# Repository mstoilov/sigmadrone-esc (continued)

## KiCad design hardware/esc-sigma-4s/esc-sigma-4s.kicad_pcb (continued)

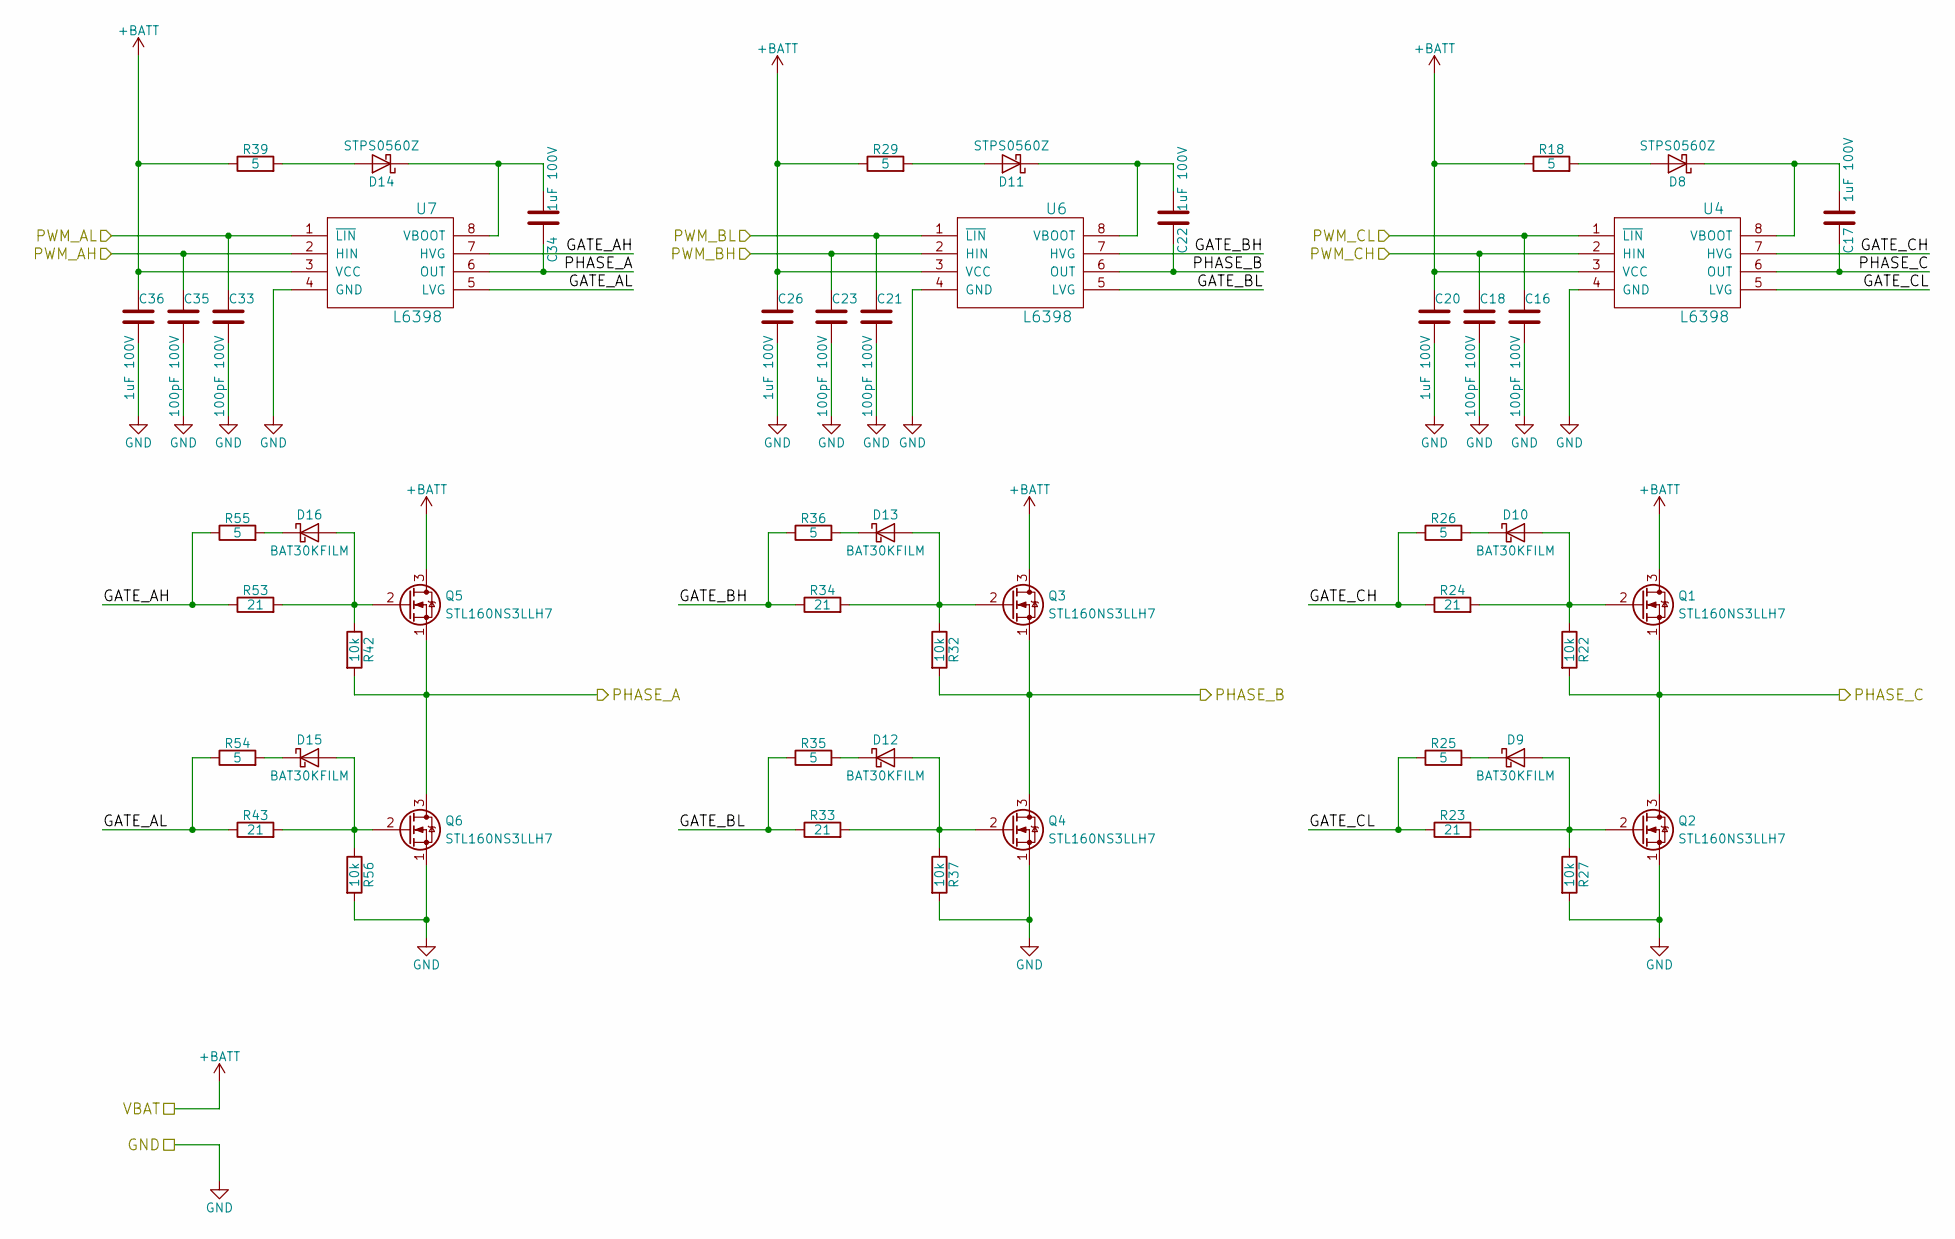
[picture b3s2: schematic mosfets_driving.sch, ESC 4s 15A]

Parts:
C16, C18, C21, C23, C33, C35: 100pF 100V; C_0603; Part 399-7821-2-ND
C17, C20, C22, C26, C34, C36: 1uF 100V; C_0805; Part 445-8887-1-ND
D8, D11, D14: STPS0560Z; D_SOD-123; Part 497-3787-1-ND
D9, D10, D12, D13, D15, D16: BAT30KFILM; D_SOD-523; Part 497-5552-1-ND
Q1, Q2, Q3, Q4, Q5, Q6: STL160NS3LLH7; PQFN_5x6_SGD; Part 497-14988-6-ND
R18, R25, R26, R29, R35, R36, R39, R54, R55: 5; R_0603; Part 311-4.99HRCT-ND
R22, R27, R32, R37, R42, R56: 10k; R_0603; Part 311-10.0KHRCT-ND
R23, R24, R33, R34, R43, R53: 21; R_0603; Part 311-21.0HRCT-ND
U4, U6, U7: L6398; SOIC-8_3.9x4.9mm_Pitch1.27mm; Part 497-16166-5-ND

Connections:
+BATT: C20.2, C26.2, C36.2, Q1.3 (D), Q3.3 (D), Q5.3 (D), R18.1, R29.1, R39.1, U4.3 (VCC), U6.3 (VCC), U7.3 (VCC); also elsewhere on the board
/MCU/PWM_AH: C35.2, U7.2 (HIN); also elsewhere on the board
/MCU/PWM_AL: C33.2, U7.1 (~LIN); also elsewhere on the board
/MCU/PWM_BH: C23.2, U6.2 (HIN); also elsewhere on the board
/MCU/PWM_BL: C21.2, U6.1 (~LIN); also elsewhere on the board
/MCU/PWM_CH: C18.2, U4.2 (HIN); also elsewhere on the board
/MCU/PWM_CL: C16.2, U4.1 (~LIN); also elsewhere on the board
/MOSFETs/GATE_AH: R53.1, R55.1, U7.7 (HVG)
/MOSFETs/GATE_AL: R43.1, R54.1, U7.5 (LVG)
/MOSFETs/GATE_BH: R34.1, R36.1, U6.7 (HVG)
/MOSFETs/GATE_BL: R33.1, R35.1, U6.5 (LVG)
/MOSFETs/GATE_CH: R24.1, R26.1, U4.7 (HVG)
/MOSFETs/GATE_CL: R23.1, R25.1, U4.5 (LVG)
/MOSFETs/PHASE_A: C34.1, Q5.1 (S), Q6.3 (D), R42.2, U7.6 (OUT); also elsewhere on the board
/MOSFETs/PHASE_B: C22.1, Q3.1 (S), Q4.3 (D), R32.2, U6.6 (OUT); also elsewhere on the board
/MOSFETs/PHASE_C: C17.1, Q1.1 (S), Q2.3 (D), R22.2, U4.6 (OUT); also elsewhere on the board
GND: C16.1, C18.1, C20.1, C21.1, C23.1, C26.1, C33.1, C35.1, C36.1, Q2.1 (S), Q4.1 (S), Q6.1 (S), R27.2, R37.2, R56.2, U4.4 (GND), U6.4 (GND), U7.4 (GND); also elsewhere on the board
unnamed: C17.2, D8.1 (K), U4.8 (VBOOT)
unnamed: C22.2, D11.1 (K), U6.8 (VBOOT)
unnamed: C34.2, D14.1 (K), U7.8 (VBOOT)
unnamed: D8.2 (A), R18.2
unnamed: D9.1 (K), R25.2
unnamed: D9.2 (A), Q2.2 (G), R23.2, R27.1
unnamed: D10.1 (K), R26.2
unnamed: D10.2 (A), Q1.2 (G), R22.1, R24.2
unnamed: D11.2 (A), R29.2
unnamed: D12.1 (K), R35.2
unnamed: D12.2 (A), Q4.2 (G), R33.2, R37.1
unnamed: D13.1 (K), R36.2
unnamed: D13.2 (A), Q3.2 (G), R32.1, R34.2
unnamed: D14.2 (A), R39.2
unnamed: D15.1 (K), R54.2
unnamed: D15.2 (A), Q6.2 (G), R43.2, R56.1
unnamed: D16.1 (K), R55.2
unnamed: D16.2 (A), Q5.2 (G), R42.1, R53.2

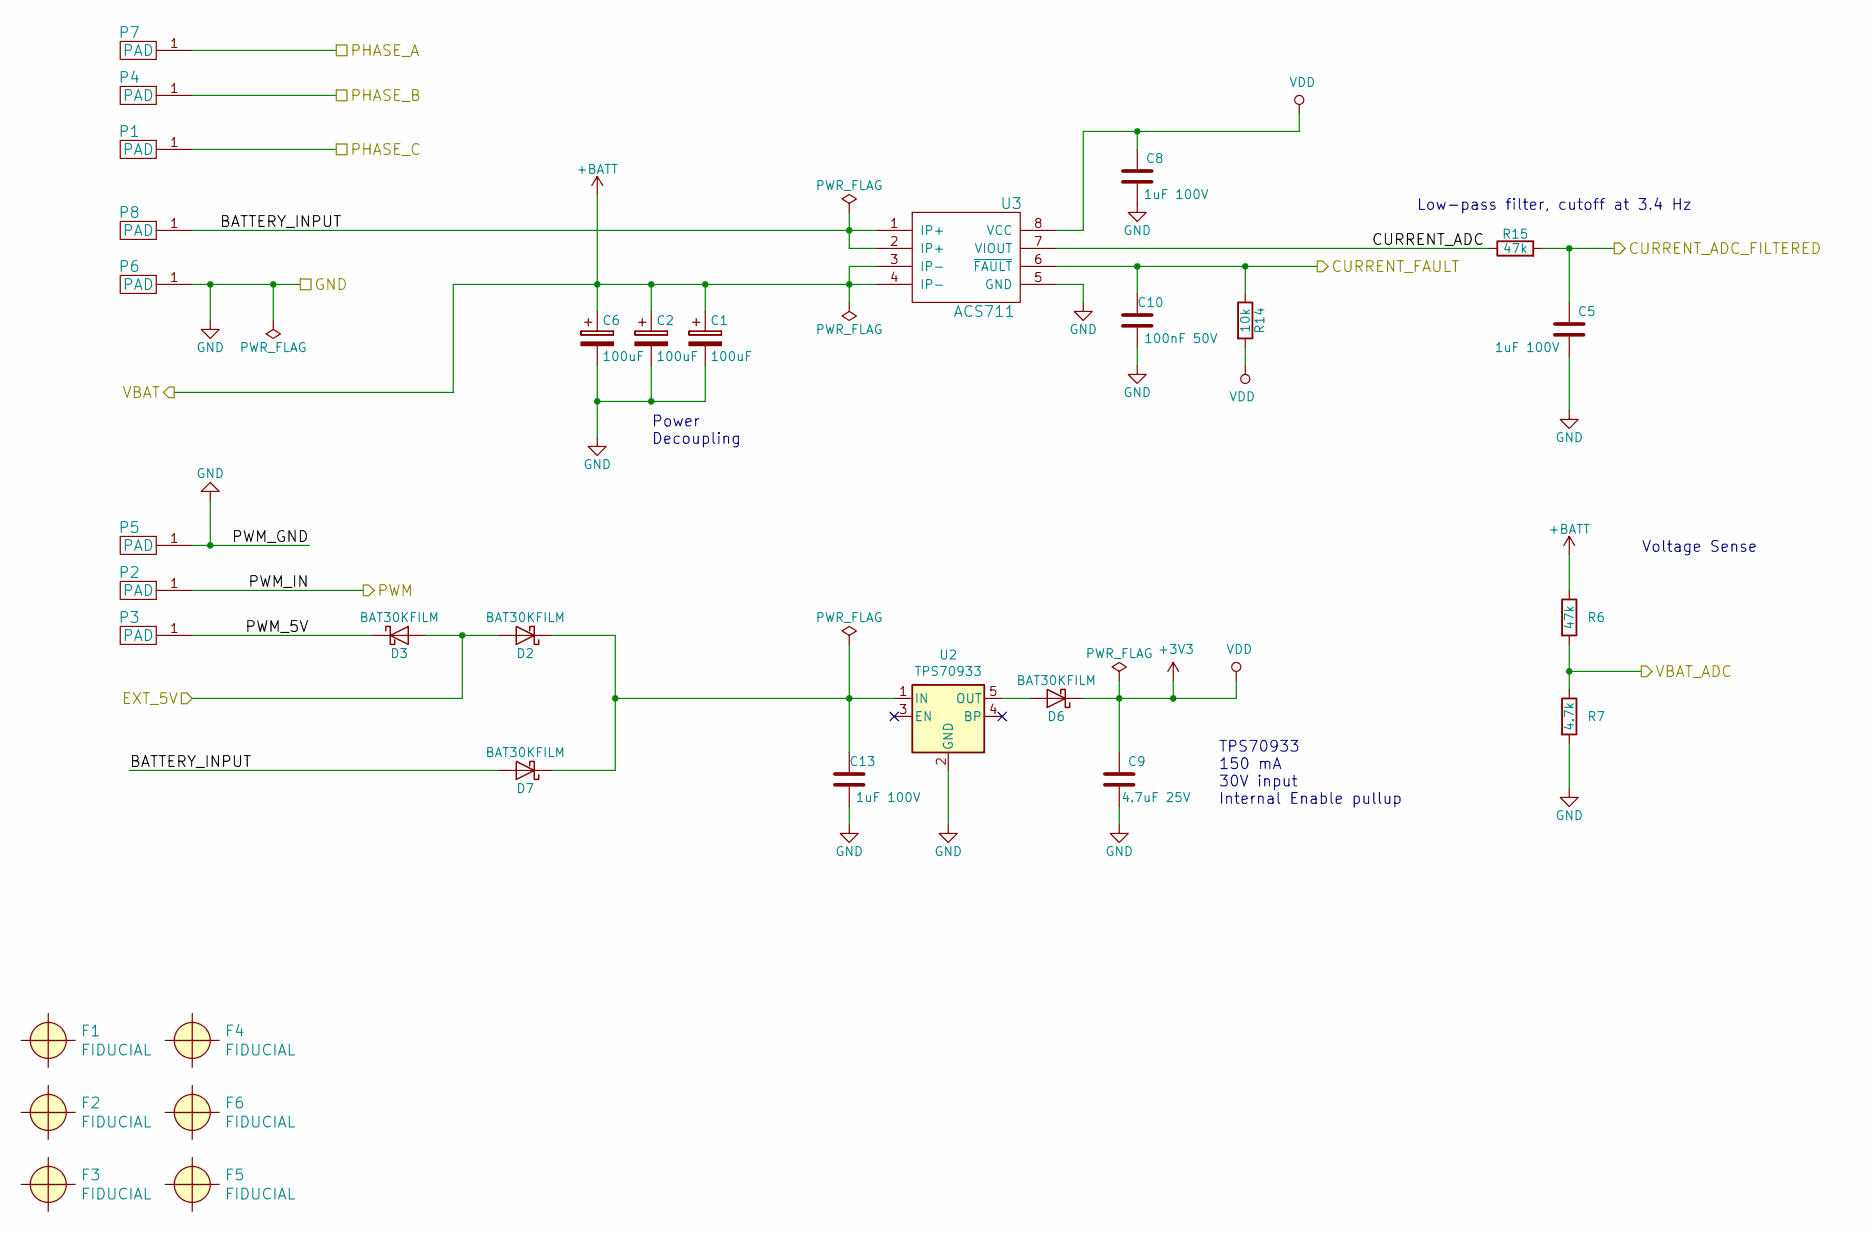
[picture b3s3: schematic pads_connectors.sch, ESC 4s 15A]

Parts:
C1, C2, C6: 100uF; CP_Elec_6.3x7.7; Part 732-8511-1-ND
C5, C8, C13: 1uF 100V; C_0805; Part 445-8887-1-ND
C9: 4.7uF 25V; C_0805; Part 1276-2415-1-ND
C10: 100nF 50V; C_0603; Part 490-4779-2-ND
D2, D3, D6, D7: BAT30KFILM; D_SOD-523; Part 497-5552-1-ND
F1, F2, F3, F4, F5, F6: FIDUCIAL; Fiducial_0.5mm_Dia_1mm_Outer
P1, P4, P6, P7, P8: PAD; SolderWirePad_single_SMD_2x3mm
P2, P3, P5: PAD; SolderWirePad_single_SMD_1.5x2.5mm
R6, R15: 47k; R_0603; Part 311-47KDCT-ND
R7: 4.7k; R_0603; Part 311-2606-2-ND
R14: 10k; R_0603; Part 311-10.0KHRCT-ND
U2: TPS70933; SOT-23-5; Part 296-35483-1-ND
U3: ACS711; SOIC-8_3.9x4.9mm_Pitch1.27mm; Part 620-1373-1-ND

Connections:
+3V3: C8.2, C9.2, D6.1 (K), R14.2, U3.8 (VCC); also elsewhere on the board
+BATT: C1.1, C2.1, C6.1, R6.1, U3.3 (IP-), U3.4 (IP-); also elsewhere on the board
/MCU/CURRENT_ADC: C5.2, R15.2; also elsewhere on the board
/MCU/CURRENT_FAULT: C10.2, R14.1, U3.6 (~FAULT); also elsewhere on the board
/MCU/EXT_5V: D2.2 (A), D3.2 (A); also elsewhere on the board
/MCU/PWM: P2.1; also elsewhere on the board
/MCU/VBAT_ADC: R6.2, R7.1; also elsewhere on the board
/MOSFETs/PHASE_A: P7.1; also elsewhere on the board
/MOSFETs/PHASE_B: P4.1; also elsewhere on the board
/MOSFETs/PHASE_C: P1.1; also elsewhere on the board
/PADS & POWER/BATTERY_INPUT: D7.2 (A), P8.1, U3.1 (IP+), U3.2 (IP+)
/PADS & POWER/CURRENT_ADC: R15.1, U3.7 (VIOUT)
/PADS & POWER/PWM_5V: D3.1 (K), P3.1
GND: C1.2, C2.2, C5.1, C6.2, C8.1, C9.1, C10.1, C13.1, P5.1, P6.1, R7.2, U2.2 (GND), U3.5 (GND); also elsewhere on the board
unnamed: C13.2, D2.1 (K), D7.1 (K), U2.1 (IN)
unnamed: D6.2 (A), U2.5 (OUT)

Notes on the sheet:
Low-pass filter, cutoff at 3.4 Hz
Power Decoupling
Voltage Sense
TPS70933 150 mA 30V input Internal Enable pullup

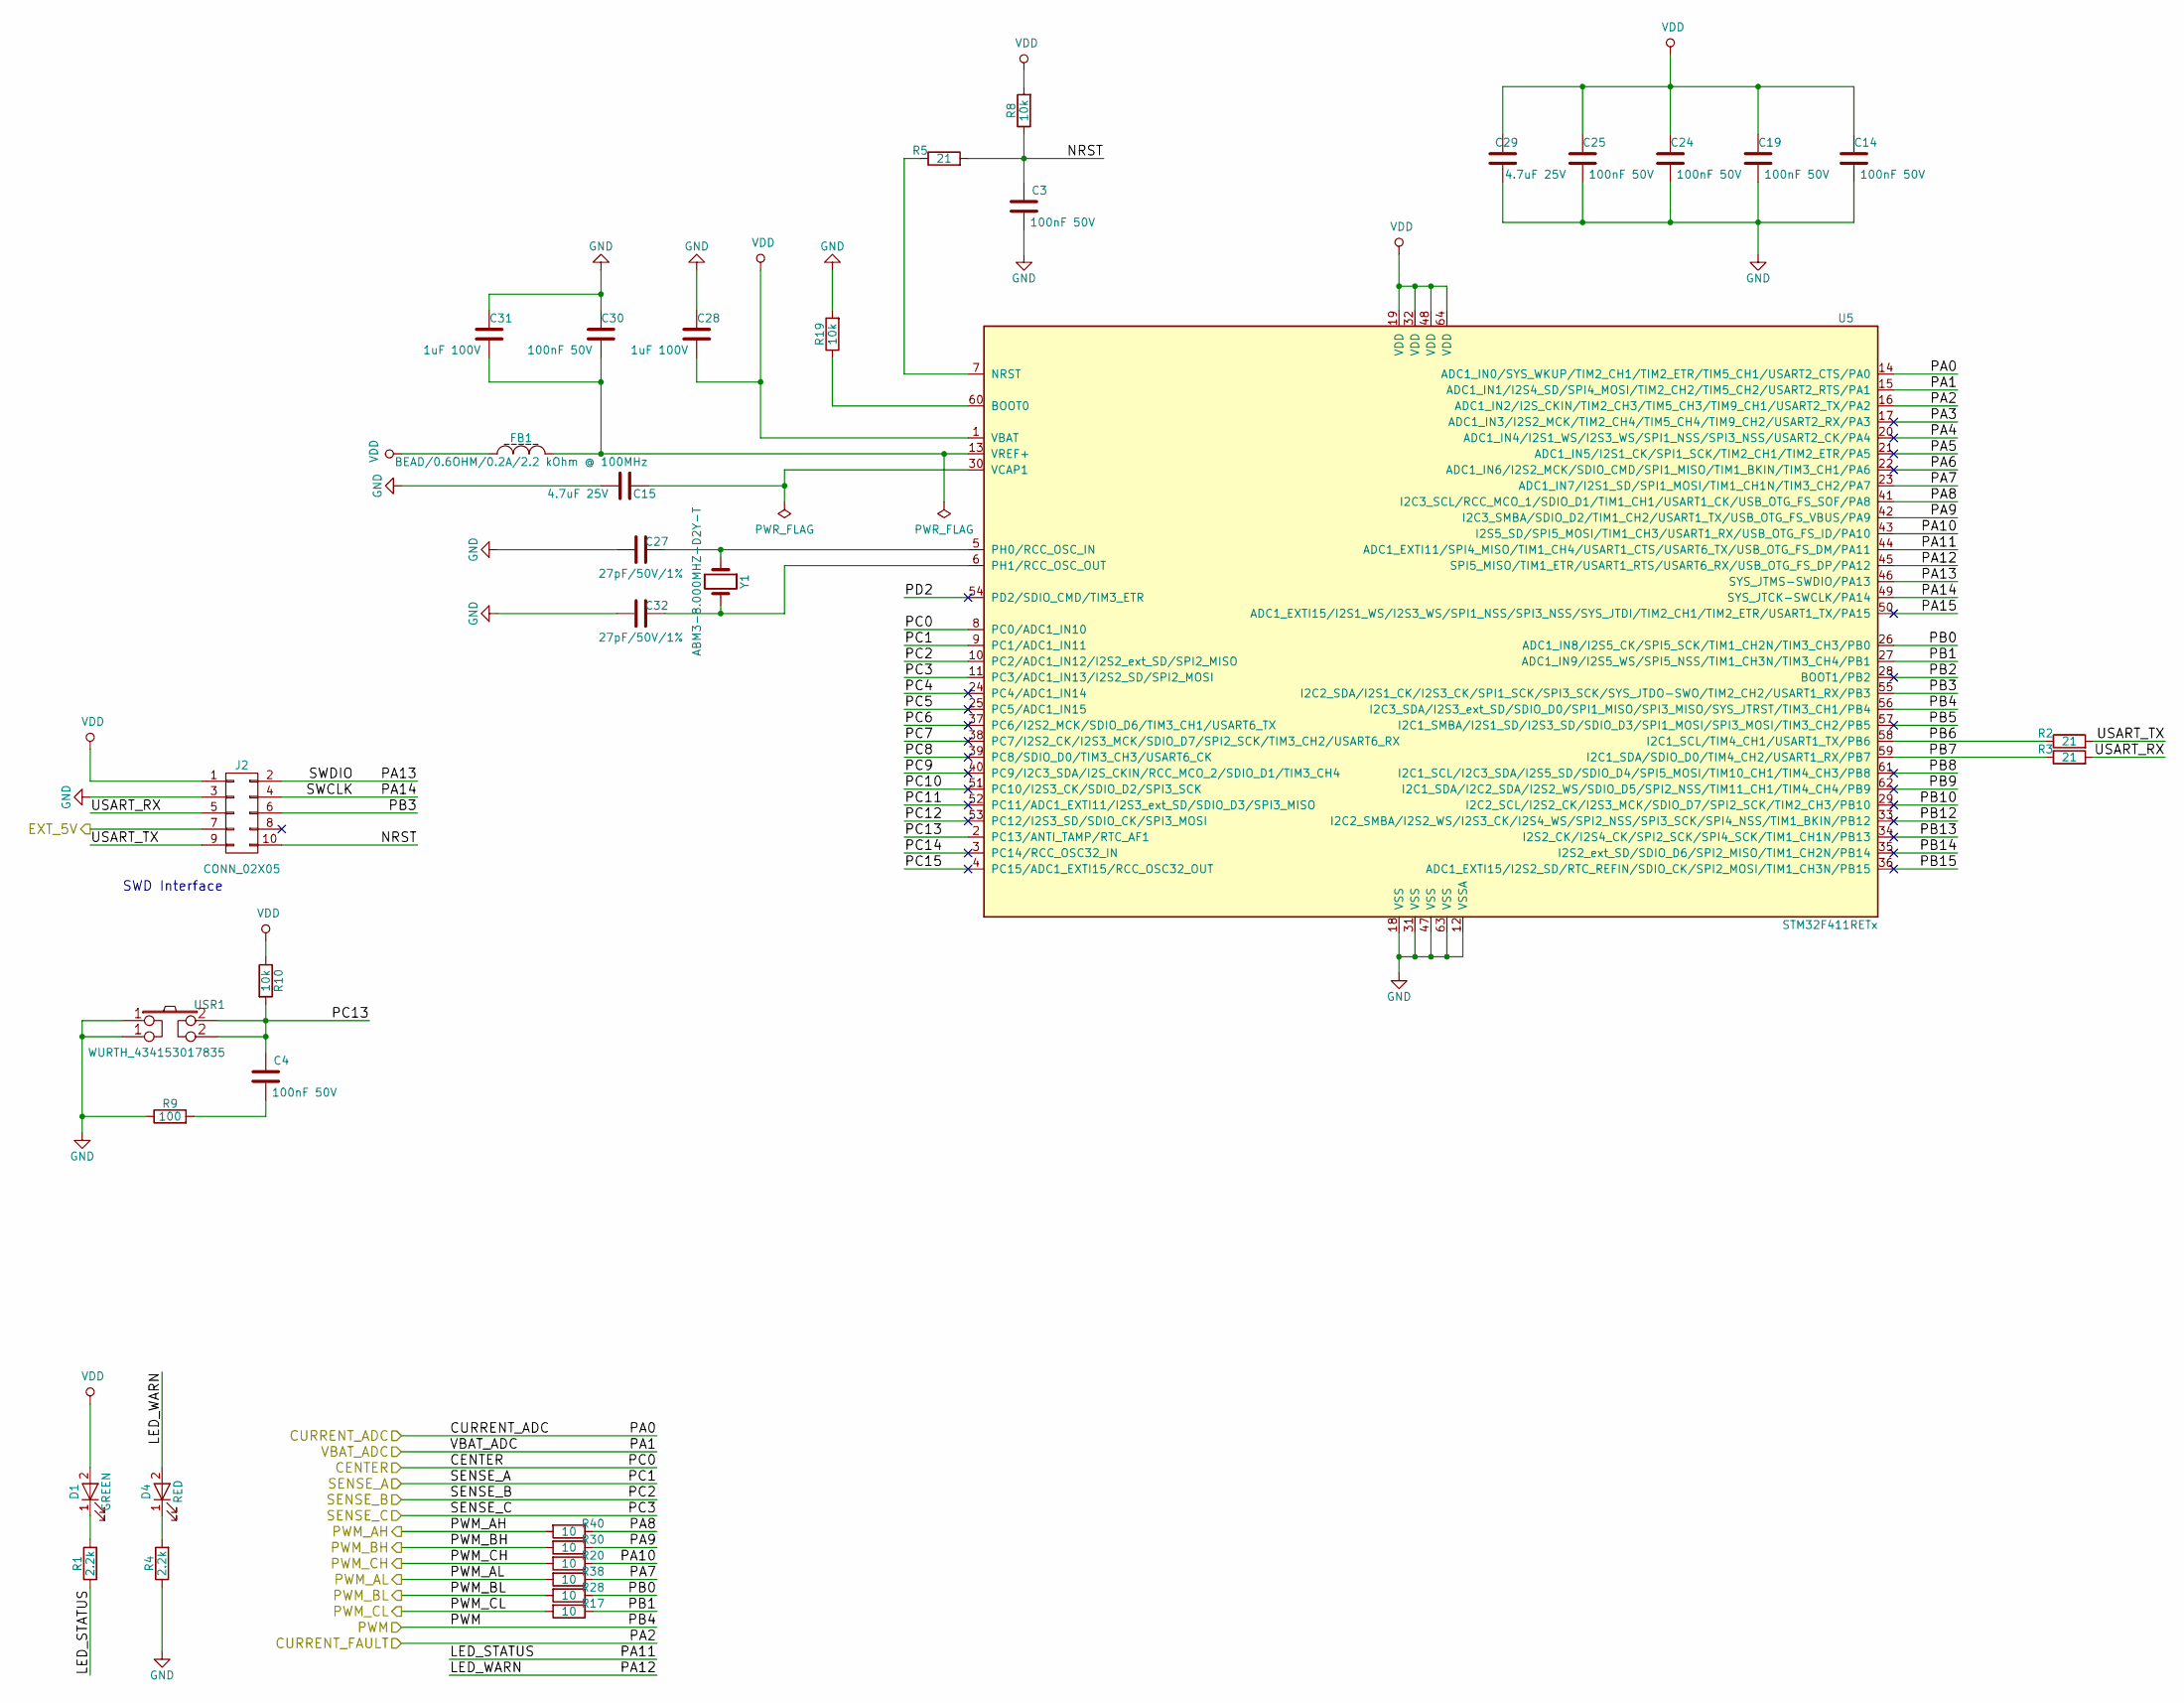
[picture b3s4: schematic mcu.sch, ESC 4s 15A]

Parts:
C3, C4, C14, C19, C24, C25, C30: 100nF 50V; C_0603; Part 490-4779-2-ND
C15, C29: 4.7uF 25V; C_0805; Part 1276-2415-1-ND
C27, C32: 27pF/50V/1%; C_0603; Part 490-9719-1-ND
C28, C31: 1uF 100V; C_0805; Part 445-8887-1-ND
D1: GREEN; LED_0603; Part 732-4971-1-ND
D4: RED; LED_0603; Part 732-4978-1-ND
FB1: BEAD/0.6OHM/0.2A/2.2 kOhm @ 100MHz; R_0805; Part 732-1609-1-ND
J2: CONN_02X05; Pin_Header_Straight_2x05_Pitch1.27mm; Part 732-5374-ND
R1, R4: 2.2k; R_0603; Part RMCF0603JT2K20CT-ND
R2, R3, R5: 21; R_0603; Part 311-21.0HRCT-ND
R8, R10, R19: 10k; R_0603; Part 311-10.0KHRCT-ND
R9: 100; R_0603; Part 311-100HRCT-ND
R17, R20, R28, R30, R38, R40: 10; R_0603; Part 311-10.0HRCT-ND
U5: STM32F411RETx; LQFP-64_10x10mm_Pitch0.5mm; Part 497-14909-ND
USR1: WURTH_434153017835; SW_SPST_WURTH_434153017835; Part 732-10143-1-ND
Y1: ABM3-8.000MHZ-D2Y-T; Crystal_SMD_Abracon_ABM3-2pin_5.0x3.2mm; Part 535-10630-1-ND

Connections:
+3V3: C14.2, C19.2, C24.2, C25.2, C28.1, C29.2, D1.2 (A), FB1.1, J2.1, R8.2, R10.1, U5.1 (VBAT), U5.19 (VDD), U5.32 (VDD), U5.48 (VDD), U5.64 (VDD); also elsewhere on the board
/MCU/CENTER: U5.8 (PC0/ADC1_IN10); also elsewhere on the board
/MCU/CURRENT_ADC: U5.14 (ADC1_IN0/SYS_WKUP/TIM2_CH1/TIM2_ETR/TIM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); also elsewhere on the board
/MCU/CURRENT_FAULT: U5.16 (ADC1_IN2/I2S_CKIN/TIM2_CH3/TIM5_CH3/TIM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); also elsewhere on the board
/MCU/EXT_5V: J2.7; also elsewhere on the board
/MCU/LED_STATUS: R1.1, U5.44 (ADC1_EXTI11/SPI4_MISO/TIM1_CH4/USART1_C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)
/MCU/LED_WARN: D4.2 (A), U5.45 (SPI5_MISO/TIM1_ETR/USART1_RTS/USART6_RX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)
/MCU/NRST: C3.2, J2.10, R5.2, R8.1
/MCU/PA3: U5.17 (ADC1_IN3/I2S2_MCK/TIM2_CH4/TIM5_CH4/TIM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)
/MCU/PA4: U5.20 (ADC1_IN4/I2S1_WS/I2S3_WS/SPI1_NSS/SPI3_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)
/MCU/PA5: U5.21 (ADC1_IN5/I2S1_CK/SPI1_SCK/TIM2_CH1/TIM2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)
/MCU/PA6: U5.22 (ADC1_IN6/I2S2_MCK/SDIO_CMD/SPI1_MISO/TI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)
/MCU/PA7: R38.1, U5.23 (ADC1_IN7/I2S1_SD/SPI1_MOSI/TIM1_CH1N/TI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)
/MCU/PA8: R40.1, U5.41 (I2C3_SCL/RCC_MCO_1/SDIO_D1/TIM1_CH1/USA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)
/MCU/PA9: R30.1, U5.42 (I2C3_SMBA/SDIO_D2/TIM1_CH2/USART1_TX/US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)
/MCU/PA10: R20.1, U5.43 (I2S5_SD/SPI5_MOSI/TIM1_CH3/USART1_RX/US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)
/MCU/PA13: J2.2, U5.46 (SYS_JTMS-SWDIO/PA13)
/MCU/PA14: J2.4, U5.49 (SYS_JTCK-SWCLK/PA14)
/MCU/PA15: U5.50 (ADC1_EXTI15/I2S1_WS/I2S3_WS/SPI1_NSS/SP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)
/MCU/PB0: R28.1, U5.26 (ADC1_IN8/I2S5_CK/SPI5_SCK/TIM1_CH2N/TIM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)
/MCU/PB1: R17.1, U5.27 (ADC1_IN9/I2S5_WS/SPI5_NSS/TIM1_CH3N/TIM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)
/MCU/PB2: U5.28 (BOOT1/PB2)
/MCU/PB3: J2.6, U5.55 (I2C2_SDA/I2S1_CK/I2S3_CK/SPI1_SCK/SPI3_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)
/MCU/PB5: U5.57 (I2C1_SMBA/I2S1_SD/I2S3_SD/SDIO_D3/SPI1_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)
/MCU/PB6: R2.1, U5.58 (I2C1_SCL/TIM4_CH1/USART1_TX/PB6)
/MCU/PB7: R3.1, U5.59 (I2C1_SDA/SDIO_D0/TIM4_CH2/USART1_RX/PB7)
/MCU/PB8: U5.61 (I2C1_SCL/I2C3_SDA/I2S5_SD/SDIO_D4/SPI5_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)
/MCU/PB9: U5.62 (I2C1_SDA/I2C2_SDA/I2S2_WS/SDIO_D5/SPI2_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)
/MCU/PB10: U5.29 (I2C2_SCL/I2S2_CK/I2S3_MCK/SDIO_D7/SPI2_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)
/MCU/PB12: U5.33 (I2C2_SMBA/I2S2_WS/I2S3_CK/I2S4_WS/SPI2_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)
/MCU/PB13: U5.34 (I2S2_CK/I2S4_CK/SPI2_SCK/SPI4_SCK/TIM1_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)
/MCU/PB14: U5.35 (I2S2_ext_SD/SDIO_D6/SPI2_MISO/TIM1_CH2N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)
/MCU/PB15: U5.36 (ADC1_EXTI15/I2S2_SD/RTC_REFIN/SDIO_CK/S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)
/MCU/PC4: U5.24 (PC4/ADC1_IN14)
/MCU/PC5: U5.25 (PC5/ADC1_IN15)
/MCU/PC6: U5.37 (PC6/I2S2_MCK/SDIO_D6/TIM3_CH1/USART6_TX)
/MCU/PC7: U5.38 (PC7/I2S2_CK/I2S3_MCK/SDIO_D7/SPI2_SCK/T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)
/MCU/PC8: U5.39 (PC8/SDIO_D0/TIM3_CH3/USART6_CK)
/MCU/PC9: U5.40 (PC9/I2C3_SDA/I2S_CKIN/RCC_MCO_2/SDIO_D1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)
/MCU/PC10: U5.51 (PC10/I2S3_CK/SDIO_D2/SPI3_SCK)
/MCU/PC11: U5.52 (PC11/ADC1_EXTI11/I2S3_ext_SD/SDIO_D3/SP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)
/MCU/PC12: U5.53 (PC12/I2S3_SD/SDIO_CK/SPI3_MOSI)
/MCU/PC13: C4.2, R10.2, U5.2 (PC13/ANTI_TAMP/RTC_AF1), USR1.2
/MCU/PC14: U5.3 (PC14/RCC_OSC32_IN)
/MCU/PC15: U5.4 (PC15/ADC1_EXTI15/RCC_OSC32_OUT)
/MCU/PD2: U5.54 (PD2/SDIO_CMD/TIM3_ETR)
/MCU/PWM: U5.56 (I2C3_SDA/I2S3_ext_SD/SDIO_D0/SPI1_MISO/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); also elsewhere on the board
/MCU/PWM_AH: R40.2; also elsewhere on the board
/MCU/PWM_AL: R38.2; also elsewhere on the board
/MCU/PWM_BH: R30.2; also elsewhere on the board
/MCU/PWM_BL: R28.2; also elsewhere on the board
/MCU/PWM_CH: R20.2; also elsewhere on the board
/MCU/PWM_CL: R17.2; also elsewhere on the board
/MCU/SENSE_A: U5.9 (PC1/ADC1_IN11); also elsewhere on the board
/MCU/SENSE_B: U5.10 (PC2/ADC1_IN12/I2S2_ext_SD/SPI2_MISO); also elsewhere on the board
/MCU/SENSE_C: U5.11 (PC3/ADC1_IN13/I2S2_SD/SPI2_MOSI); also elsewhere on the board
/MCU/USART_RX: J2.5, R3.2
/MCU/USART_TX: J2.9, R2.2
/MCU/VBAT_ADC: U5.15 (ADC1_IN1/I2S4_SD/SPI4_MOSI/TIM2_CH2/TIM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); also elsewhere on the board
GND: C3.1, C14.1, C15.1, C19.1, C24.1, C25.1, C27.2, C28.2, C29.1, C30.2, C31.2, C32.2, J2.3, R4.1, R9.1, R19.2, U5.12 (VSSA), U5.18 (VSS), U5.31 (VSS), U5.47 (VSS), U5.63 (VSS), USR1.1; also elsewhere on the board
unnamed: C4.1, R9.2
unnamed: C15.2, U5.30 (VCAP1)
unnamed: C27.1, U5.5 (PH0/RCC_OSC_IN), Y1.1
unnamed: C30.1, C31.1, FB1.2, U5.13 (VREF+)
unnamed: C32.1, U5.6 (PH1/RCC_OSC_OUT), Y1.2
unnamed: D1.1 (K), R1.2
unnamed: D4.1 (K), R4.2
unnamed: R5.1, U5.7 (NRST)
unnamed: R19.1, U5.60 (BOOT0)

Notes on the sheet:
SWD Interface

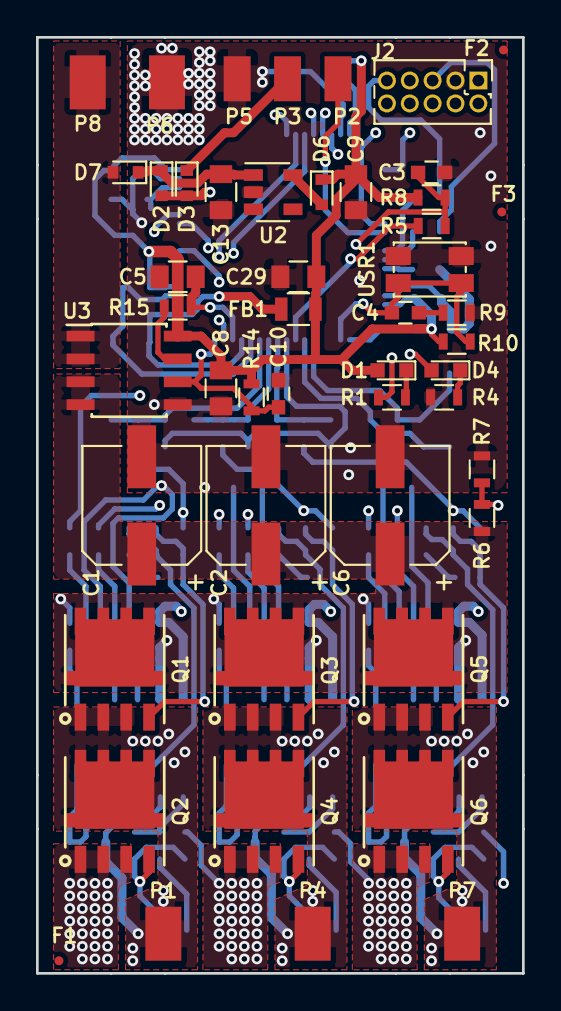
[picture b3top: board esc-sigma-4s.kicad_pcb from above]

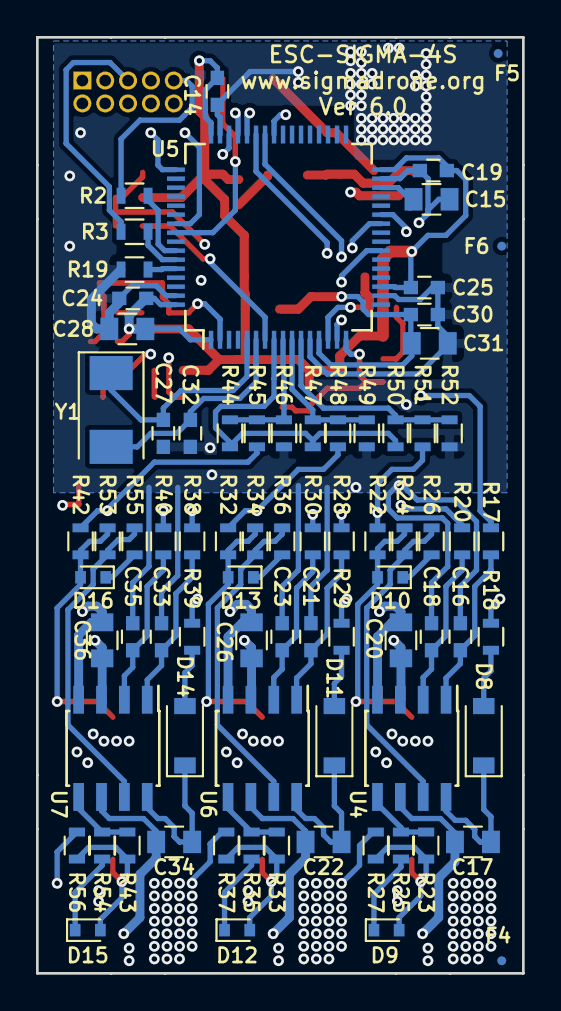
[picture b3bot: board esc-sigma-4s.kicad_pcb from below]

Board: 4 copper layers, 27.0 x 52.0 mm, 127 parts (78 on the bottom side), 76 nets.

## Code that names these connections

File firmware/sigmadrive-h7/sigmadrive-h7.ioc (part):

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Mcu.Name=STM32H743VGTx
Mcu.Package=LQFP100
Mcu.UserName=STM32H743VGTx
PA0.GPIOParameters=GPIO_Label
PA0.GPIO_Label=PULSE_M2/TIM5_CH1
PA0.Signal=S_TIM5_CH1
PA1.GPIOParameters=GPIO_PuPd,GPIO_Label,GPIO_Mode
PA1.GPIO_Label=M1_SOA/M1_IA_FB
PA1.GPIO_Mode=GPIO_MODE_ANALOG
PA1.GPIO_PuPd=GPIO_NOPULL
PA1.Mode=IN17-Single-Ended
PA1.Signal=ADC1_INP17
PA10.GPIOParameters=GPIO_Speed,GPIO_Label
PA10.GPIO_Label=DBG_USART1_TX
PA10.GPIO_Speed=GPIO_SPEED_FREQ_VERY_HIGH
PA10.Mode=Asynchronous
PA10.Signal=USART1_RX
PA11.GPIOParameters=GPIO_Label
PA11.GPIO_Label=USB_DM
PA11.Mode=Device_Only
PA11.Signal=USB_OTG_FS_DM
PA12.GPIOParameters=GPIO_Label
PA12.GPIO_Label=USB_DP
PA12.Mode=Device_Only
PA12.Signal=USB_OTG_FS_DP
PA13\ (JTMS/SWDIO).Signal=DEBUG_JTMS-SWDIO
PA14\ (JTCK/SWCLK).Signal=DEBUG_JTCK-SWCLK
PA2.GPIOParameters=GPIO_PuPd,GPIO_Label,GPIO_Mode
PA2.GPIO_Label=M1_SOB/M1_IB_FB
PA2.GPIO_Mode=GPIO_MODE_ANALOG
PA2.GPIO_PuPd=GPIO_NOPULL
PA2.Signal=ADCx_INP14
PA3.GPIOParameters=GPIO_PuPd,GPIO_Label,GPIO_Mode
PA3.GPIO_Label=ANALOG_SPEED_CTRL
PA3.GPIO_Mode=GPIO_MODE_ANALOG
PA3.GPIO_PuPd=GPIO_NOPULL
PA3.Signal=ADCx_INP15
PA4.GPIOParameters=GPIO_PuPd,GPIO_Label,GPIO_Mode
PA4.GPIO_Label=M1_SOC/M1_IC_FB
PA4.GPIO_Mode=GPIO_MODE_ANALOG
PA4.GPIO_PuPd=GPIO_NOPULL
PA4.Signal=ADCx_INP18
PA5.GPIOParameters=GPIO_Label
PA5.GPIO_Label=PULSE_M1/TIM2_CH1
PA5.Signal=S_TIM2_CH1_ETR
PA6.GPIOParameters=GPIO_PuPd,GPIO_Label,GPIO_Mode
PA6.GPIO_Label=VBAT_ADC
PA6.GPIO_Mode=GPIO_MODE_ANALOG
PA6.GPIO_PuPd=GPIO_NOPULL
PA6.Signal=ADCx_INP3
PA7.GPIOParameters=GPIO_Label
PA7.GPIO_Label=M2_AL
PA7.Mode=PWM Generation1 CH1 CH1N
PA7.Signal=TIM8_CH1N
PA9.GPIOParameters=GPIO_Speed,GPIO_Label
PA9.GPIO_Label=DBG_USART1_RX
PA9.GPIO_Speed=GPIO_SPEED_FREQ_VERY_HIGH
PA9.Mode=Asynchronous
PA9.Signal=USART1_TX
PB0.Signal=S_TIM3_CH3
PB1.GPIOParameters=GPIO_Label
PB1.GPIO_Label=M2_CL
PB1.Mode=PWM Generation3 CH3 CH3N
PB1.Signal=TIM8_CH3N
PB10.Mode=Full_Duplex_Master
PB10.Signal=SPI2_SCK
PB11.GPIOParameters=GPIO_Label
PB11.GPIO_Label=QUAD_Z_M1
PB11.Signal=GPXTI11
PB12.GPIOParameters=GPIO_Label
PB12.GPIO_Label=OUTPUT_1
PB12.Signal=GPIO_Output
PB13.GPIOParameters=GPIO_Label
PB13.GPIO_Label=OUTPUT_2
PB13.Signal=GPIO_Output
PB14.GPIOParameters=GPIO_Label
PB14.GPIO_Label=M2_BL
PB14.Mode=PWM Generation2 CH2 CH2N
PB14.Signal=TIM8_CH2N
PB15.GPIOParameters=GPIO_Label
PB15.GPIO_Label=DRV_SDI
PB15.Mode=Full_Duplex_Master
PB15.Signal=SPI2_MOSI
PB2.GPIOParameters=GPIO_Label
PB2.GPIO_Label=GATE_M2_ENABLE
PB2.Signal=GPIO_Output
PB3\ (JTDO/TRACESWO).Signal=DEBUG_JTDO-SWO
PB4\ (NJTRST).GPIOParameters=GPIO_Label
PB4\ (NJTRST).GPIO_Label=QUAD_A_M1
PB4\ (NJTRST).Signal=S_TIM3_CH1
PB5.GPIOParameters=GPIO_Label
PB5.GPIO_Label=QUAD_B_M1
PB5.Signal=S_TIM3_CH2
PB6.GPIOParameters=GPIO_Label
PB6.GPIO_Label=QUAD_A_M2
PB6.Signal=S_TIM4_CH1
PB7.GPIOParameters=GPIO_Label
PB7.GPIO_Label=QUAD_B_M2
PB7.Signal=S_TIM4_CH2
PB8.Signal=S_TIM4_CH3
PC0.GPIOParameters=GPIO_Label
PC0.GPIO_Label=M2_SOA/M2_IA_FB
PC0.Signal=ADCx_INP10
PC1.GPIOParameters=GPIO_Label
PC1.GPIO_Label=M2_SOB/M2_IB_FB
PC1.Signal=ADCx_INP11
PC10.GPIOParameters=GPIO_Label
PC10.GPIO_Label=TD_422/UART4
PC10.Mode=Asynchronous
PC10.Signal=UART4_TX
PC11.GPIOParameters=GPIO_Label
PC11.GPIO_Label=RD_422/UART4
PC11.Mode=Asynchronous
PC11.Signal=UART4_RX
PC12.GPIOParameters=GPIO_Label
PC12.GPIO_Label=BRAKE_B_RELEASE
PC12.Signal=GPIO_Output
PC13.GPIOParameters=GPIO_Label
PC13.GPIO_Label=DRV1_CS
PC13.Signal=GPIO_Output
PC14-OSC32_IN\ (OSC32_IN).GPIOParameters=GPIO_Label
PC14-OSC32_IN\ (OSC32_IN).GPIO_Label=DRV2_CS
PC14-OSC32_IN\ (OSC32_IN).Signal=GPIO_Output
PC15-OSC32_OUT\ (OSC32_OUT).GPIOParameters=GPIO_Label
PC15-OSC32_OUT\ (OSC32_OUT).GPIO_Label=DRV_FAULT\#
PC15-OSC32_OUT\ (OSC32_OUT).Signal=GPIO_Input
PC2_C.GPIOParameters=GPIO_Label
PC2_C.GPIO_Label=DRV_SDO
PC2_C.Mode=Full_Duplex_Master
PC2_C.Signal=SPI2_MISO
PC3_C.GPIOParameters=GPIO_Label
PC3_C.GPIO_Label=M2_SOC/M2_IC_FB
PC3_C.Mode=IN1-Single-Ended
PC3_C.Signal=ADC3_INP1
PC4.GPIOParameters=GPIO_PuPd,GPIO_Label,GPIO_Mode
PC4.GPIO_Label=TEMP2
PC4.GPIO_Mode=GPIO_MODE_ANALOG
PC4.GPIO_PuPd=GPIO_NOPULL
PC4.Signal=ADCx_INP4
PC5.GPIOParameters=GPIO_PuPd,GPIO_Label,GPIO_Mode
PC5.GPIO_Label=TEMP1
PC5.GPIO_Mode=GPIO_MODE_ANALOG
PC5.GPIO_PuPd=GPIO_NOPULL
PC5.Signal=ADCx_INP8
PC6.GPIOParameters=GPIO_Label
PC6.GPIO_Label=M2_AH
PC6.Signal=S_TIM8_CH1
PC7.GPIOParameters=GPIO_Label
PC7.GPIO_Label=M2_BH
PC7.Signal=S_TIM8_CH2
PC8.GPIOParameters=GPIO_Label
PC8.GPIO_Label=M2_CH
PC8.Signal=S_TIM8_CH3
PC9.GPIOParameters=GPIO_Label
PC9.GPIO_Label=LED_STATUS
PC9.Signal=GPIO_Output
PD0.GPIOParameters=GPIO_Label
PD0.GPIO_Label=CAR_RX
PD0.Mode=FDCAN_Activate
PD0.Signal=FDCAN1_RX
PD1.GPIOParameters=GPIO_Label
PD1.GPIO_Label=CAN_TX
PD1.Mode=FDCAN_Activate
PD1.Signal=FDCAN1_TX
PD10.GPIOParameters=GPIO_Label
PD10.GPIO_Label=M1_SW1
PD10.Signal=GPIO_Input
PD11.GPIOParameters=GPIO_Label
PD11.GPIO_Label=M1_SW2
PD11.Signal=GPIO_Input
PD12.GPIOParameters=GPIO_Label
PD12.GPIO_Label=ENCODER_DE_M1
PD12.Mode=Hardware Flow Control (RS485)
PD12.Signal=USART3_DE
PD13.GPIOParameters=GPIO_Label
PD13.GPIO_Label=DIRECTION_A
PD13.Signal=GPIO_Input
PD14.GPIOParameters=GPIO_Label
PD14.GPIO_Label=LED_WARN
PD14.Signal=GPIO_Output
PD15.GPIOParameters=GPIO_Label
PD15.GPIO_Label=DIRECTION_B
PD15.Signal=GPIO_Input
PD2.GPIOParameters=GPIO_Label
PD2.GPIO_Label=M2_SW1
PD2.Signal=GPIO_Input
PD3.GPIOParameters=GPIO_Label
PD3.GPIO_Label=M2_SW2
PD3.Signal=GPIO_Input
PD4.GPIOParameters=GPIO_Label
PD4.GPIO_Label=ENCODER_DE_M2
PD4.Mode=Hardware Flow Control (RS485)
PD4.Signal=USART2_DE
PD5.GPIOParameters=GPIO_Label
PD5.GPIO_Label=ENCODER_DI_M2
PD5.Mode=Asynchronous
PD5.Signal=USART2_TX
PD6.GPIOParameters=GPIO_Label
PD6.GPIO_Label=ENCODER_RO_M2
PD6.Mode=Asynchronous
PD6.Signal=USART2_RX
PD7.GPIOParameters=GPIO_Label
PD7.GPIO_Label=QUAD_Z_M2
PD7.Signal=GPXTI7
PD8.GPIOParameters=GPIO_Label
PD8.GPIO_Label=ENCODER_DI_M1
PD8.Mode=Asynchronous
PD8.Signal=USART3_TX
PD9.GPIOParameters=GPIO_Label
PD9.GPIO_Label=ENCODER_RO_M1
PD9.Mode=Asynchronous
PD9.Signal=USART3_RX
PE0.GPIOParameters=GPIO_Speed
PE0.GPIO_Speed=GPIO_SPEED_FREQ_VERY_HIGH
PE0.Mode=Asynchronous
PE0.Signal=UART8_RX
PE1.GPIOParameters=GPIO_Speed
PE1.GPIO_Speed=GPIO_SPEED_FREQ_VERY_HIGH
PE1.Mode=Asynchronous
PE1.Signal=UART8_TX
PE10.GPIOParameters=GPIO_Label
PE10.GPIO_Label=M1_BL
PE10.Mode=PWM Generation2 CH2 CH2N
PE10.Signal=TIM1_CH2N
PE11.GPIOParameters=GPIO_Label
PE11.GPIO_Label=M1_BH
PE11.Signal=S_TIM1_CH2
PE12.GPIOParameters=GPIO_Label
PE12.GPIO_Label=M1_CL
PE12.Mode=PWM Generation3 CH3 CH3N
PE12.Signal=TIM1_CH3N
PE13.GPIOParameters=GPIO_Label
PE13.GPIO_Label=M1_CH
PE13.Signal=S_TIM1_CH3
PE14.GPIOParameters=GPIO_Label
PE14.GPIO_Label=DRV_CAL
PE14.Signal=GPIO_Output
PE15.GPIOParameters=GPIO_Label
PE15.GPIO_Label=GATE_M1_ENABLE
PE15.Signal=GPIO_Output
PE2.GPIOParameters=GPIO_Label
PE2.GPIO_Label=INPUT_1\#
PE2.Signal=GPIO_Input
PE4.GPIOParameters=GPIO_Label
PE4.GPIO_Label=INPUT_2\#
PE4.Signal=GPIO_Input
PE5.GPIOParameters=GPIO_Label
PE5.GPIO_Label=BRAKE_A_FB
PE5.Signal=GPIO_Input
PE6.GPIOParameters=GPIO_Label
PE6.GPIO_Label=BRAKE_B_FB
PE6.Signal=GPIO_Input
PE8.GPIOParameters=GPIO_Label
PE8.GPIO_Label=M1_AL
PE8.Mode=PWM Generation1 CH1 CH1N
PE8.Signal=TIM1_CH1N
PE9.GPIOParameters=GPIO_Label
PE9.GPIO_Label=M1_AH
PE9.Signal=S_TIM1_CH1
PH0-OSC_IN\ (PH0).Mode=HSE-External-Oscillator
PH0-OSC_IN\ (PH0).Signal=RCC_OSC_IN
PH1-OSC_OUT\ (PH1).Mode=HSE-External-Oscillator
PH1-OSC_OUT\ (PH1).Signal=RCC_OSC_OUT
RCC.HSE_VALUE=12000000
RCC.SYSCLKFreq_VALUE=480000000
RCC.SYSCLKSource=RCC_SYSCLKSOURCE_PLLCLK
board=custom

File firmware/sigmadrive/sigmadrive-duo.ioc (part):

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Mcu.Name=STM32F745V(E-G)Tx
Mcu.Package=LQFP100
Mcu.UserName=STM32F745VGTx
PA0/WKUP.Signal=S_TIM5_CH1
PA1.GPIOParameters=GPIO_Label
PA1.GPIO_Label=M1_IA_FB
PA1.Signal=ADCx_IN1
PA10.Mode=Asynchronous
PA10.Signal=USART1_RX
PA11.Mode=Device_Only
PA11.Signal=USB_OTG_FS_DM
PA12.Mode=Device_Only
PA12.Signal=USB_OTG_FS_DP
PA15.Mode=Hardware Flow Control (RS485)
PA15.Signal=UART4_DE
PA2.GPIOParameters=GPIO_Label
PA2.GPIO_Label=M1_IB_FB
PA2.Signal=ADCx_IN2
PA3.GPIOParameters=GPIO_Label
PA3.GPIO_Label=ADC3_IN3
PA3.Signal=ADCx_IN3
PA4.GPIOParameters=GPIO_Label
PA4.GPIO_Label=M1_IC_FB
PA4.Signal=ADCx_IN4
PA5.Signal=S_TIM2_CH1_ETR
PA6.Signal=ADCx_IN6
PA7.Mode=PWM Generation1 CH1 CH1N
PA7.Signal=TIM8_CH1N
PA9.Mode=Asynchronous
PA9.Signal=USART1_TX
PB0.Signal=S_TIM3_CH3
PB1.Mode=PWM Generation3 CH3 CH3N
PB1.Signal=TIM8_CH3N
PB10.Mode=Full_Duplex_Master
PB10.Signal=SPI2_SCK
PB14.Mode=PWM Generation2 CH2 CH2N
PB14.Signal=TIM8_CH2N
PB15.Mode=Full_Duplex_Master
PB15.Signal=SPI2_MOSI
PB2.GPIOParameters=GPIO_Label
PB2.GPIO_Label=GATE2_ENABLE
PB2.Signal=GPIO_Output
PB4.Signal=S_TIM3_CH1
PB5.Signal=S_TIM3_CH2
PB6.Signal=S_TIM4_CH1
PB7.Signal=S_TIM4_CH2
PB8.Signal=S_TIM4_CH3
PB9.Signal=GPIO_Output
PC0.GPIOParameters=GPIO_Label
PC0.GPIO_Label=M2_IA_FB
PC0.Signal=ADCx_IN10
PC1.GPIOParameters=GPIO_Label
PC1.GPIO_Label=M2_IB_FB
PC1.Signal=ADCx_IN11
PC10.Mode=Asynchronous
PC10.Signal=UART4_TX
PC11.Mode=Asynchronous
PC11.Signal=UART4_RX
PC12.GPIOParameters=GPIO_Label
PC12.GPIO_Label=SYNC_STAT
PC12.Signal=GPIO_Output
PC13.GPIOParameters=PinState,GPIO_PuPd,GPIO_Label
PC13.GPIO_Label=DRV1_CS
PC13.GPIO_PuPd=GPIO_PULLUP
PC13.PinState=GPIO_PIN_SET
PC13.Signal=GPIO_Output
PC14/OSC32_IN.GPIOParameters=PinState,GPIO_PuPd,GPIO_Label
PC14/OSC32_IN.GPIO_Label=DRV2_CS
PC14/OSC32_IN.GPIO_PuPd=GPIO_PULLUP
PC14/OSC32_IN.PinState=GPIO_PIN_SET
PC14/OSC32_IN.Signal=GPIO_Output
PC15/OSC32_OUT.GPIOParameters=GPIO_Label
PC15/OSC32_OUT.GPIO_Label=DRV_FAULT
PC15/OSC32_OUT.Signal=GPXTI15
PC2.Mode=Full_Duplex_Master
PC2.Signal=SPI2_MISO
PC3.GPIOParameters=GPIO_Label
PC3.GPIO_Label=M2_IC_FB
PC3.Signal=ADCx_IN13
PC4.GPIOParameters=GPIO_Label
PC4.GPIO_Label=TEMP2
PC4.Signal=ADCx_IN14
PC5.GPIOParameters=GPIO_Label
PC5.GPIO_Label=TEMP1
PC5.Signal=ADCx_IN15
PC6.Signal=S_TIM8_CH1
PC7.Signal=S_TIM8_CH2
PC8.Signal=S_TIM8_CH3
PC9.GPIOParameters=PinState,GPIO_Label
PC9.GPIO_Label=LED_STATUS
PC9.PinState=GPIO_PIN_SET
PC9.Signal=GPIO_Output
PD0.GPIOParameters=GPIO_Label
PD0.GPIO_Label=SYNC_CMD1
PD0.Signal=GPIO_Input
PD1.GPIOParameters=GPIO_Label
PD1.GPIO_Label=SYNC_CMD2
PD1.Signal=GPIO_Input
PD10.GPIOParameters=GPIO_Label
PD10.GPIO_Label=M1_SW1
PD10.Signal=GPIO_Input
PD11.GPIOParameters=GPIO_Label
PD11.GPIO_Label=M1_SW2
PD11.Signal=GPIO_Input
PD12.GPIOParameters=GPIO_Label
PD12.GPIO_Label=M2_ENCODER_DE
PD12.Mode=Hardware Flow Control (RS485)
PD12.Signal=USART3_DE
PD14.GPIOParameters=GPIO_Speed,PinState,GPIO_PuPd,GPIO_Label
PD14.GPIO_Label=LED_WARN
PD14.GPIO_PuPd=GPIO_PULLUP
PD14.GPIO_Speed=GPIO_SPEED_FREQ_LOW
PD14.PinState=GPIO_PIN_RESET
PD14.Signal=GPIO_Output
PD2.GPIOParameters=GPIO_Label
PD2.GPIO_Label=M2_SW2
PD2.Signal=GPIO_Input
PD4.Mode=Hardware Flow Control (RS485)
PD4.Signal=USART2_DE
PD5.Mode=Asynchronous
PD5.Signal=USART2_TX
PD6.Mode=Asynchronous
PD6.Signal=USART2_RX
PD7.GPIOParameters=GPIO_PuPd,GPIO_Label,GPIO_ModeDefaultEXTI
PD7.GPIO_Label=M1_QUAD_Z
PD7.GPIO_ModeDefaultEXTI=GPIO_MODE_IT_RISING
PD7.GPIO_PuPd=GPIO_PULLDOWN
PD7.Signal=GPXTI7
PD8.GPIOParameters=GPIO_Label
PD8.GPIO_Label=M2_ENCODER_DI
PD8.Mode=Asynchronous
PD8.Signal=USART3_TX
PD9.GPIOParameters=GPIO_Label
PD9.GPIO_Label=M2_ENCODER_RO
PD9.Mode=Asynchronous
PD9.Signal=USART3_RX
PE0.Mode=Asynchronous
PE0.Signal=UART8_RX
PE1.Mode=Asynchronous
PE1.Signal=UART8_TX
PE11.Signal=S_TIM1_CH2
PE13.Signal=S_TIM1_CH3
PE14.GPIOParameters=PinState,GPIO_Label
PE14.GPIO_Label=DRV_CAL
PE14.PinState=GPIO_PIN_SET
PE14.Signal=GPIO_Output
PE15.GPIOParameters=GPIO_Label
PE15.GPIO_Label=GATE1_ENABLE
PE15.Signal=GPIO_Output
PE2.Signal=GPIO_Input
PE3.Signal=GPIO_Input
PE4.Signal=GPIO_Input
PE5.Signal=GPIO_Output
PE6.Signal=GPIO_Output
PE8.Mode=PWM Generation1 CH1 CH1N
PE8.Signal=TIM1_CH1N
PE9.Signal=S_TIM1_CH1
PH0/OSC_IN.Mode=HSE-External-Oscillator
PH0/OSC_IN.Signal=RCC_OSC_IN
PH1/OSC_OUT.Mode=HSE-External-Oscillator
PH1/OSC_OUT.Signal=RCC_OSC_OUT
RCC.HSE_VALUE=12000000
RCC.SYSCLKFreq_VALUE=216000000
RCC.SYSCLKSource=RCC_SYSCLKSOURCE_PLLCLK
board=custom

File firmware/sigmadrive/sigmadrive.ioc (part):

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Mcu.Name=STM32F745V(E-G)Tx
Mcu.Package=LQFP100
Mcu.UserName=STM32F745VGTx
PA0/WKUP.Signal=S_TIM5_CH1
PA1.Signal=ADCx_IN1
PA10.Mode=Asynchronous
PA10.Signal=USART1_RX
PA11.Mode=Device_Only
PA11.Signal=USB_OTG_FS_DM
PA12.Mode=Device_Only
PA12.Signal=USB_OTG_FS_DP
PA15.Mode=Hardware Flow Control (RS485)
PA15.Signal=UART4_DE
PA2.Signal=ADCx_IN2
PA4.Signal=ADCx_IN4
PA5.Signal=S_TIM2_CH1_ETR
PA6.Signal=ADCx_IN6
PA7.Mode=PWM Generation1 CH1 CH1N
PA7.Signal=TIM8_CH1N
PA8.GPIOParameters=GPIO_Label,GPIO_ModeDefaultEXTI
PA8.GPIO_Label=USER_BTN
PA8.GPIO_ModeDefaultEXTI=GPIO_MODE_IT_FALLING
PA8.Signal=GPXTI8
PA9.Mode=Asynchronous
PA9.Signal=USART1_TX
PB0.Signal=S_TIM3_CH3
PB1.Mode=PWM Generation3 CH3 CH3N
PB1.Signal=TIM8_CH3N
PB10.Mode=Full_Duplex_Master
PB10.Signal=SPI2_SCK
PB14.Mode=PWM Generation2 CH2 CH2N
PB14.Signal=TIM8_CH2N
PB15.Mode=Full_Duplex_Master
PB15.Signal=SPI2_MOSI
PB2.GPIOParameters=PinState,GPIO_PuPd
PB2.GPIO_PuPd=GPIO_PULLUP
PB2.PinState=GPIO_PIN_SET
PB2.Signal=GPIO_Output
PB4.Signal=S_TIM3_CH1
PB5.Signal=S_TIM3_CH2
PB6.Signal=S_TIM4_CH1
PB7.Signal=S_TIM4_CH2
PB8.Signal=S_TIM4_CH3
PB9.Signal=GPIO_Output
PC0.Signal=ADCx_IN10
PC1.Signal=ADCx_IN11
PC10.Mode=Asynchronous
PC10.Signal=UART4_TX
PC11.Mode=Asynchronous
PC11.Signal=UART4_RX
PC12.Signal=GPIO_Output
PC13.GPIOParameters=PinState,GPIO_PuPd
PC13.GPIO_PuPd=GPIO_PULLUP
PC13.PinState=GPIO_PIN_SET
PC13.Signal=GPIO_Output
PC14/OSC32_IN.GPIOParameters=GPIO_Speed,PinState,GPIO_PuPd,GPIO_ModeDefaultOutputPP
PC14/OSC32_IN.GPIO_ModeDefaultOutputPP=GPIO_MODE_OUTPUT_PP
PC14/OSC32_IN.GPIO_PuPd=GPIO_PULLUP
PC14/OSC32_IN.GPIO_Speed=GPIO_SPEED_FREQ_LOW
PC14/OSC32_IN.PinState=GPIO_PIN_SET
PC14/OSC32_IN.Signal=GPIO_Output
PC15/OSC32_OUT.GPIOParameters=GPIO_PuPd
PC15/OSC32_OUT.GPIO_PuPd=GPIO_PULLUP
PC15/OSC32_OUT.Signal=GPIO_Input
PC2.GPIOParameters=GPIO_PuPd
PC2.GPIO_PuPd=GPIO_PULLUP
PC2.Mode=Full_Duplex_Master
PC2.Signal=SPI2_MISO
PC3.Signal=ADCx_IN13
PC4.Signal=ADCx_IN14
PC5.Signal=ADCx_IN15
PC6.Signal=S_TIM8_CH1
PC7.Signal=S_TIM8_CH2
PC8.Signal=S_TIM8_CH3
PC9.GPIOParameters=PinState,GPIO_Label
PC9.GPIO_Label=LED_STATUS
PC9.PinState=GPIO_PIN_SET
PC9.Signal=GPIO_Output
PD0.Signal=GPIO_Input
PD1.Signal=GPIO_Input
PD10.Signal=GPIO_Input
PD11.Signal=GPIO_Input
PD12.Mode=Hardware Flow Control (RS485)
PD12.Signal=USART3_DE
PD14.GPIOParameters=GPIO_Speed,PinState,GPIO_PuPd,GPIO_Label
PD14.GPIO_Label=LED_WARN
PD14.GPIO_PuPd=GPIO_PULLUP
PD14.GPIO_Speed=GPIO_SPEED_FREQ_LOW
PD14.PinState=GPIO_PIN_RESET
PD14.Signal=GPIO_Output
PD2.Signal=GPIO_Input
PD3.Signal=GPIO_Input
PD4.Mode=Hardware Flow Control (RS485)
PD4.Signal=USART2_DE
PD5.Mode=Asynchronous
PD5.Signal=USART2_TX
PD6.Mode=Asynchronous
PD6.Signal=USART2_RX
PD7.GPIOParameters=GPIO_PuPd,GPIO_Label,GPIO_ModeDefaultEXTI
PD7.GPIO_Label=ENCODER_Z
PD7.GPIO_ModeDefaultEXTI=GPIO_MODE_IT_RISING
PD7.GPIO_PuPd=GPIO_PULLDOWN
PD7.Signal=GPXTI7
PD8.Mode=Asynchronous
PD8.Signal=USART3_TX
PD9.Mode=Asynchronous
PD9.Signal=USART3_RX
PE0.Mode=Asynchronous
PE0.Signal=UART8_RX
PE1.Mode=Asynchronous
PE1.Signal=UART8_TX
PE10.Mode=PWM Generation2 CH2 CH2N
PE10.Signal=TIM1_CH2N
PE11.Signal=S_TIM1_CH2
PE12.Mode=PWM Generation3 CH3 CH3N
PE12.Signal=TIM1_CH3N
PE13.Signal=S_TIM1_CH3
PE14.GPIOParameters=PinState
PE14.PinState=GPIO_PIN_RESET
PE14.Signal=GPIO_Output
PE15.GPIOParameters=PinState,GPIO_PuPd
PE15.GPIO_PuPd=GPIO_PULLUP
PE15.PinState=GPIO_PIN_SET
PE15.Signal=GPIO_Output
PE2.Signal=GPIO_Input
PE3.Signal=GPIO_Input
PE4.Signal=GPIO_Input
PE5.Signal=GPIO_Output
PE6.Signal=GPIO_Output
PE8.Mode=PWM Generation1 CH1 CH1N
PE8.Signal=TIM1_CH1N
PE9.Signal=S_TIM1_CH1
PH0/OSC_IN.Mode=HSE-External-Oscillator
PH0/OSC_IN.Signal=RCC_OSC_IN
PH1/OSC_OUT.Mode=HSE-External-Oscillator
PH1/OSC_OUT.Signal=RCC_OSC_OUT
RCC.HSE_VALUE=12000000
RCC.SYSCLKFreq_VALUE=216000000
RCC.SYSCLKSource=RCC_SYSCLKSOURCE_PLLCLK
board=custom

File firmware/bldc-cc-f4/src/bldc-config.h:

#include "bldc-include.h"
#include "pinnames.h"

#define ACTIVE_LOW_TRUE				(1)
#define ACTIVE_LOW_FALSE			(0)

#define TIM_AMC						TIM1
#define TIM_AMC_PERIPH				LL_APB2_GRP1_PERIPH_TIM1
#define TIM_TRG						TIM2
#define TIM_TRG_PERIPH				LL_APB1_GRP1_PERIPH_TIM2
#define TIM_PWM						TIM3
#define TIM_PWM_PERIPH				LL_APB1_GRP1_PERIPH_TIM3
#define TIM_BLINK					TIM4
#define TIM_BLINK_PERIPH			LL_APB1_GRP1_PERIPH_TIM4
#define TIM_JIFFIES					TIM5
#define TIM_JIFFIES_PERIPH			LL_APB1_GRP1_PERIPH_TIM5
#define JIFFIES_HZ					1000000


#define PWM_MODE					LL_TIM_OCMODE_PWM1
#define DEAD_TIME_NS				320
#define ADC_SAMPLING_CYCLES			LL_ADC_SAMPLINGTIME_28CYCLES

//#define _ESC_MODEL_SIGMASERVO_ 1

#if _ESC_MODEL_SIGMASERVO_


#define USART_TX					PA_15
//#define USART_RX					PB_3
#define CURRENT_FAULT_PIN			PA_2

#define PWM_AL						PB_13
#define PWM_BL						PB_14
#define PWM_CL						PB_15

#define PIN_ADC1					PC_0
#define PIN_ADC2					PC_1
#define PIN_ADC3					PC_2
#define PIN_ADC4					PA_0
#define PIN_ADC5					PA_1

#define CHANNEL_PHASE_A				LL_ADC_CHANNEL_10
#define CHANNEL_PHASE_B				LL_ADC_CHANNEL_11
#define CHANNEL_PHASE_C				LL_ADC_CHANNEL_12
#define CHANNEL_CURRENT_ADC			LL_ADC_CHANNEL_0

#define ADC_A						0
#define ADC_B						1
#define ADC_C						2

#define LED_STATUS_PIN				PA_6
#define LED_WARNING_PIN				PA_5

#define PWM_AH						PA_8
#define PWM_BH						PA_9
#define PWM_CH						PA_10

#define LED_STATUS_ACTIVE_LOW		ACTIVE_LOW_TRUE

#define BTN_USER_PIN				PA_4
#define BTN_USER_IRQ				EXTI4_IRQn
#define BTN_USER_IRQ_PRIORITY		12

#define PWM_INPUT_PIN				PB_4
#define PWM_INPUT_AF				LL_GPIO_AF_2


#else

#if _ESC_MODEL_ZEKENG_

#define USART_TX					PA_15
#define USART_RX					PB_3
#define CURRENT_FAULT_PIN			PB_13

#else

#define USART_TX					PB_6
#define USART_RX					PB_7
#define CURRENT_FAULT_PIN			PA_15

#endif

#define PWM_AL						PA_7
#define PWM_BL						PB_0
#define PWM_CL						PB_1

#define PIN_ADC1					PC_1
#define PIN_ADC2					PC_2
#define PIN_ADC3					PC_3
#define PIN_ADC4					PC_0
#define PIN_ADC5					PA_0

#define CHANNEL_PHASE_A				LL_ADC_CHANNEL_13
#define CHANNEL_PHASE_B				LL_ADC_CHANNEL_12
#define CHANNEL_PHASE_C				LL_ADC_CHANNEL_11
#define CHANNEL_CENTER				LL_ADC_CHANNEL_10
#define CHANNEL_CURRENT_ADC			LL_ADC_CHANNEL_0

#define ADC_A						2
#define ADC_B						1
#define ADC_C						0

#define LED_STATUS_PIN				PA_11
#define LED_WARNING_PIN				PA_12

#define PWM_AH						PA_8
#define PWM_BH						PA_9
#define PWM_CH						PA_10

#define LED_STATUS_ACTIVE_LOW		ACTIVE_LOW_TRUE

#define BTN_USER_PIN				PC_13
#define BTN_USER_IRQ				EXTI15_10_IRQn
#define BTN_USER_IRQ_PRIORITY		12

#define PWM_INPUT_PIN				PB_4
#define PWM_INPUT_AF				LL_GPIO_AF_2

#endif


#define UART_BAUD_RATE				230400
#define VOLTAGE_MCU_POWER			3300		/* Milli-Volts */
#define BEMF_SENSE_DEVIDER			(47000/4700)
#define RES_MEASUREMENT_CYCLES		1000
#define MAX_CURRENT_MILIAPMS		30000
#define	SANITY_CHECK_VOLTAGE_RAIL	8000		/* Milli-Volts */
#define	SANITY_CHECK_VOLTAGE_BEMF	1000		/* Milli-Volts */
#define BEMF_MAX_KICKBACK_PERIOD	3
#define SINE_STATES					6
#define MECHANICAL_DEGREES_RATIO	8
#define REPETIONS_TO_UPDATE			1			/* MIN valeue: 1 */
#define MIN_MILLIHERTZ				1000
#define BOOTSTRAP_BASE_THROTTLE		10
#define BOOTSTRAP_POST_THROTTLE		40
#define MIN_THROTTLE_PERCENT		51
#define BOOTSTRAP_COUNTER_INIT		20
#define SWITCHING_FREQUENCY			100000
#define BOOTSTRAP_STAGES			30
#define BEMF_INTEGRAL_THRESHOLD		3300
#define BEMF_MEASURE_DELAY_NS		550UL
#define THROTTLE_MIN_PWM_DUTY		1100	/* Millisceonds */
#define THROTTLE_SPEED_HZ_250		400		/* Throttle speed when the throttle is at 250 Hz */
#define THROTTLE_SPEED_HZ_0			200		/* Throttle speed when the throttle is at 0 Hz */
#define START_WITH_THROTTLE
#define COMPENSATE_DATA_BIAS
//#define TEST_BOOTSTRAP
